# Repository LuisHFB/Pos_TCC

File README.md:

# Pos_TCC# Driver para Berlin Heart ExoCOR

## Abstract
Projetar circuito de driver para a bomba cardiaca usando RTOS para o controle, com redundancias.
## Berlin Heart ExoCOR

## IKUS

##

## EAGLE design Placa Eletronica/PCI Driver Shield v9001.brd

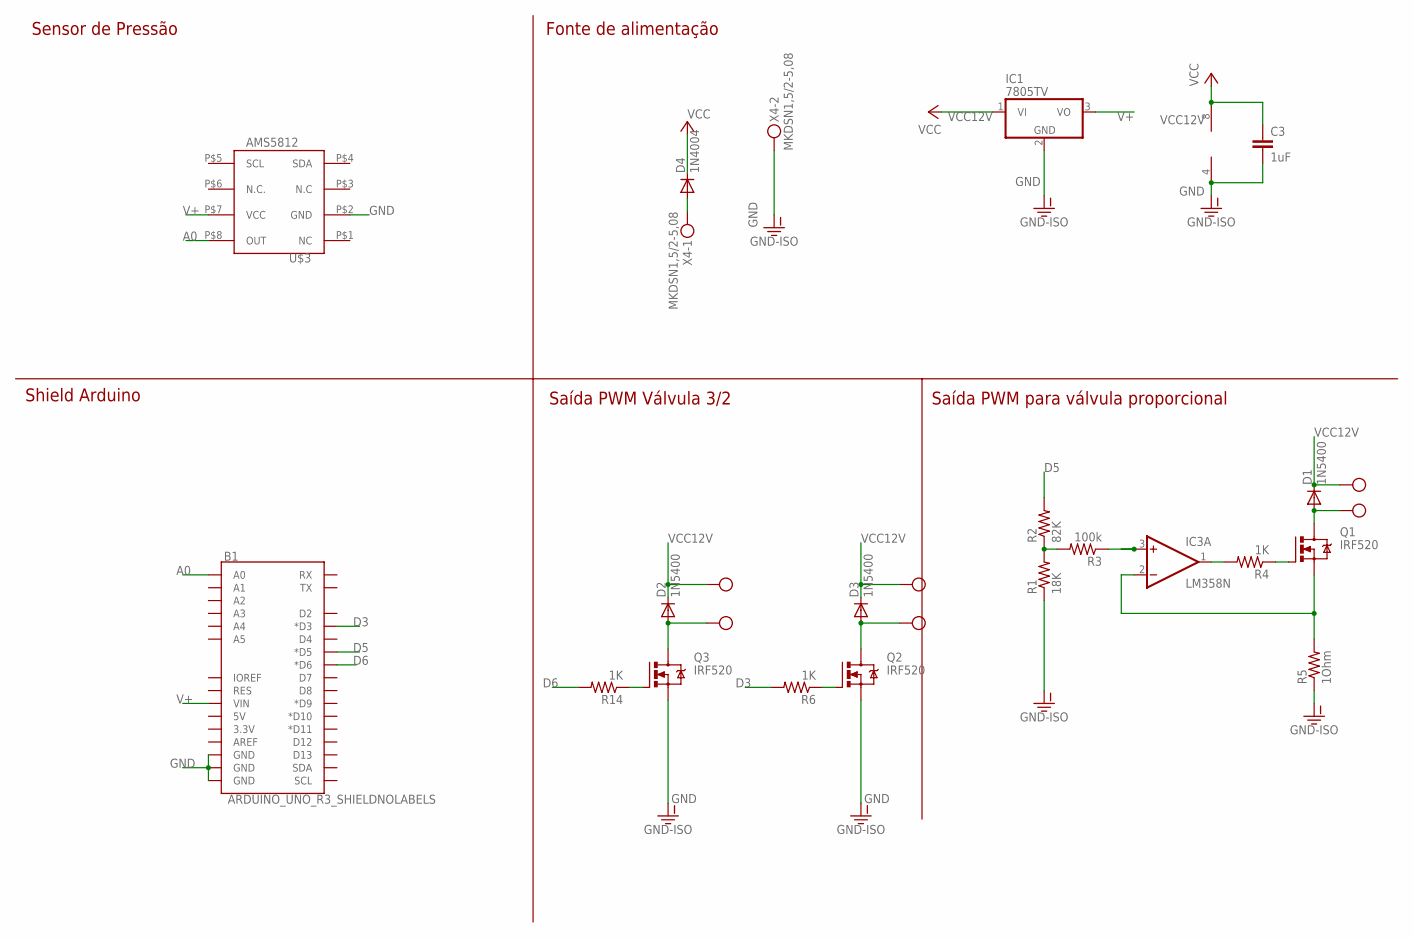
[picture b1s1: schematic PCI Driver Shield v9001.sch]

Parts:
B1: ARDUINO_UNO_R3_SHIELDNOLABELS; UNO_R3_SHIELD_NOLABELS
C3: 1uF; C2.5-4
D1, D2, D3: 1N5400; DO201-15
D4: 1N4004; DO41-10
IC1: 7805TV; TO220V
IC3: LM358N; DIL08
Q1, Q2, Q3: IRF520; TO220BV
R1: 18K; 0204/7
R2: 82K; 0204/7
R3: 100k; 0204/7
R4, R6, R14: 1K; 0204/7
R5: 1Ohm; 0204/7
S1, S2, S3: MKDSN1,5/2-5,08
U$3: AMS5812
X4: MKDSN1,5/2-5,08

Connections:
A0: B1.A0, U$3.P$8 (OUT)
D3: B1.D3 (*D3), R6.2
D5: B1.D5 (*D5), R2.2
D6: B1.D6 (*D6), R14.2
GND: B1.GND@0 (GND), B1.GND@1 (GND), B1.GND@2 (GND), C3.2, IC1.2 (GND), IC3.4 (V-), Q2.S, Q3.S, R1.1, R5.1, U$3.P$2 (GND), X4.2
GNDS1: IC3.2 (-IN), Q1.S, R5.2
unnamed: D2.A, Q3.D, S2.1
unnamed: R1.2, R2.1, R3.2
unnamed: Q1.G, R4.1
unnamed: Q2.G, R6.1
unnamed: D3.A, Q2.D, S3.1
unnamed: IC3.1 (OUT), R4.2
unnamed: D1.A, Q1.D, S1.1
unnamed: IC3.3 (+IN), R3.1
unnamed: D4.A, X4.1
unnamed: Q3.G, R14.1
V+: B1.VIN, IC1.3 (VO), U$3.P$7 (VCC)
VCC12V: C3.1, D1.C, D2.C, D3.C, D4.C, IC1.1 (VI), IC3.8 (V+), S1.2, S2.2, S3.2

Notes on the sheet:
Sensor de Pressão
Shield Arduino
Saída PWM Válvula 3/2
Fonte de alimentação
Saída PWM para válvula proporcional

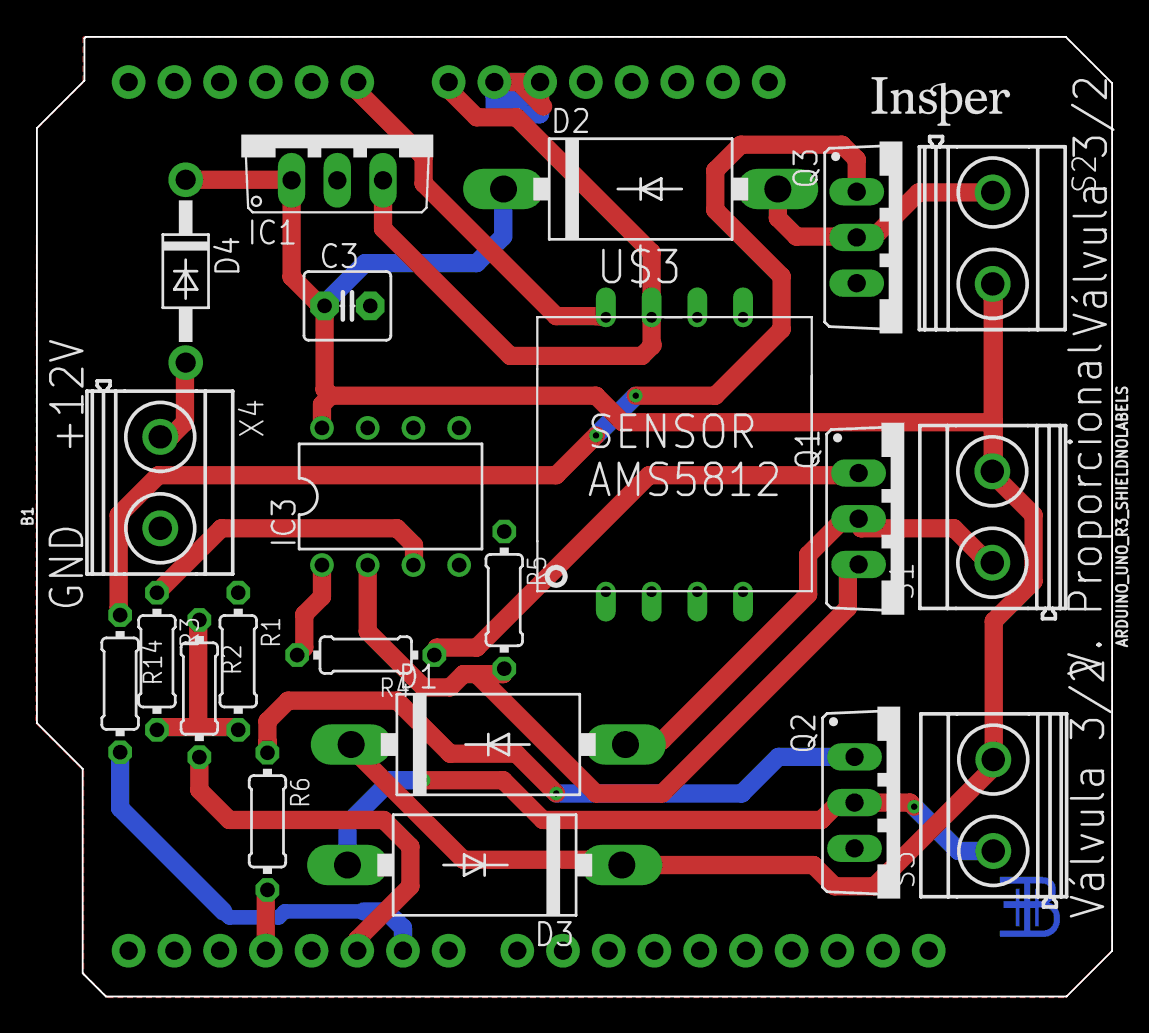
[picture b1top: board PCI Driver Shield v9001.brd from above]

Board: 2 copper layers, 59.7 x 53.3 mm, 23 parts (0 on the bottom side), 18 nets.

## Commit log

2019-12-12 First Commit
    Primeiro Commit
2019-12-12 reagge
    a
2019-12-14 Estruturando
    modificação na estrutura da apresentação
2019-12-14 Inclusão de referencias
    Adicionadas referencias
2019-12-14 Sensores + Atuadores
    Começei a adicionar alguns sensores e atuadores que utilizamos no Insper
2019-12-14 Imagens
    Add imagens
2019-12-14 Imagens no Layout
    add imagem no layout
2019-12-14 Link IMG
2019-12-14 Agora vai
    Links certo?
2019-12-16 Placa Eletronica
    Adicionado arquivo BRD e SCH da placa atual que usamos
2020-01-04 ADD AGENDA adicionada todo e agenda
2020-01-05 Troquei Readme
    Readme por proposta
2020-01-05 Atualização Prazo adicionado prazo de entrega
2020-01-05 Tags inseri tags
2020-01-15 Layout
2020-01-20 Add Normas e Tabela Cronograma
2020-01-20 Agenda "completa"
2020-01-22 Outros Aparelhos
2020-01-27 Norma 60601-1-11
2020-02-15 Considerações 60601-1-1

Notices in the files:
parts and their libraries:
SparkFun-Boards: Licensing: Creative Commons ShareAlike 4.0 International - https://creativecommons.org/licenses/by-sa/4.0
